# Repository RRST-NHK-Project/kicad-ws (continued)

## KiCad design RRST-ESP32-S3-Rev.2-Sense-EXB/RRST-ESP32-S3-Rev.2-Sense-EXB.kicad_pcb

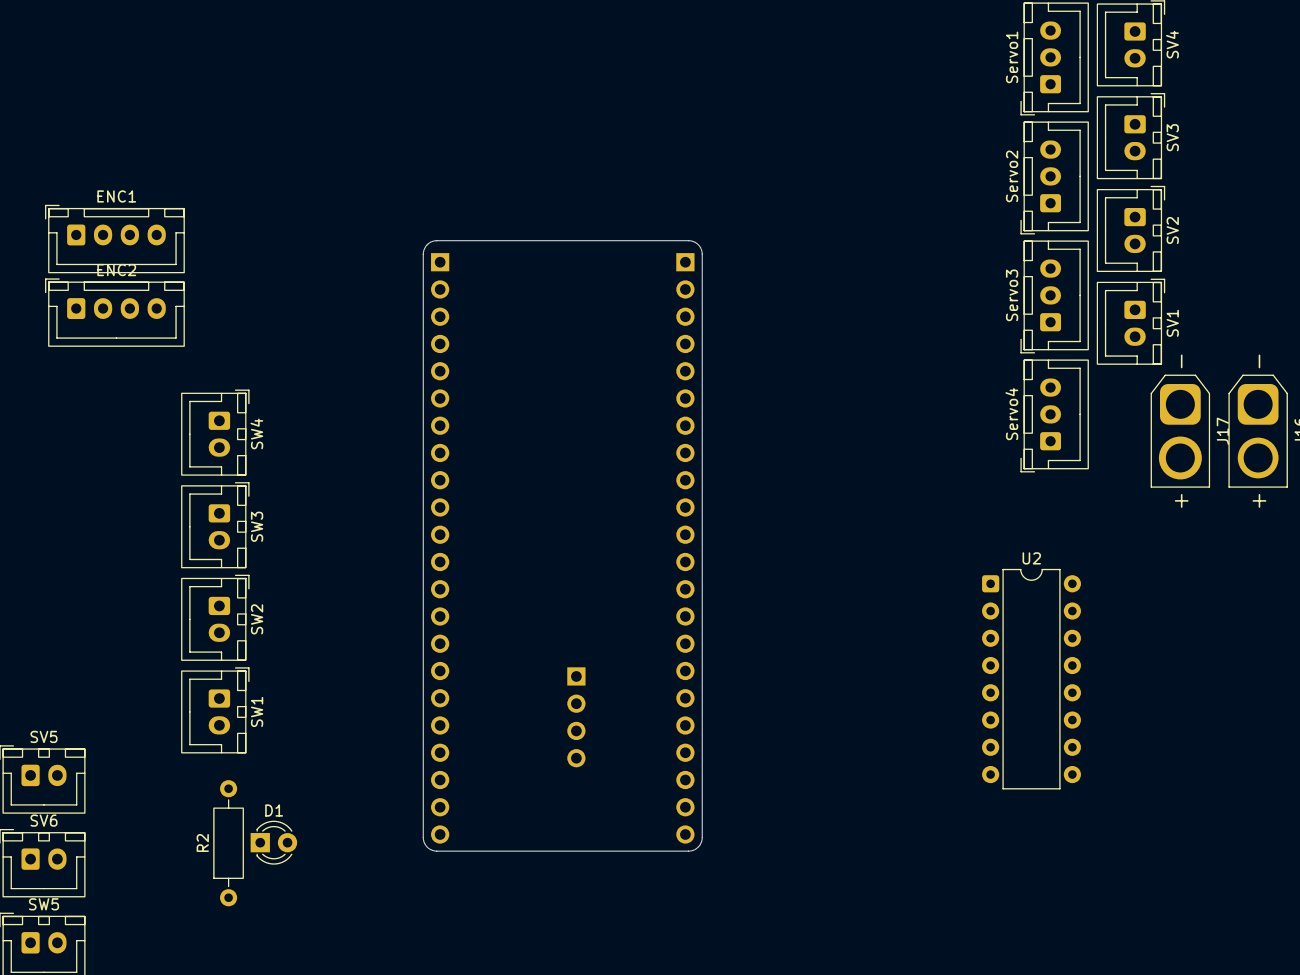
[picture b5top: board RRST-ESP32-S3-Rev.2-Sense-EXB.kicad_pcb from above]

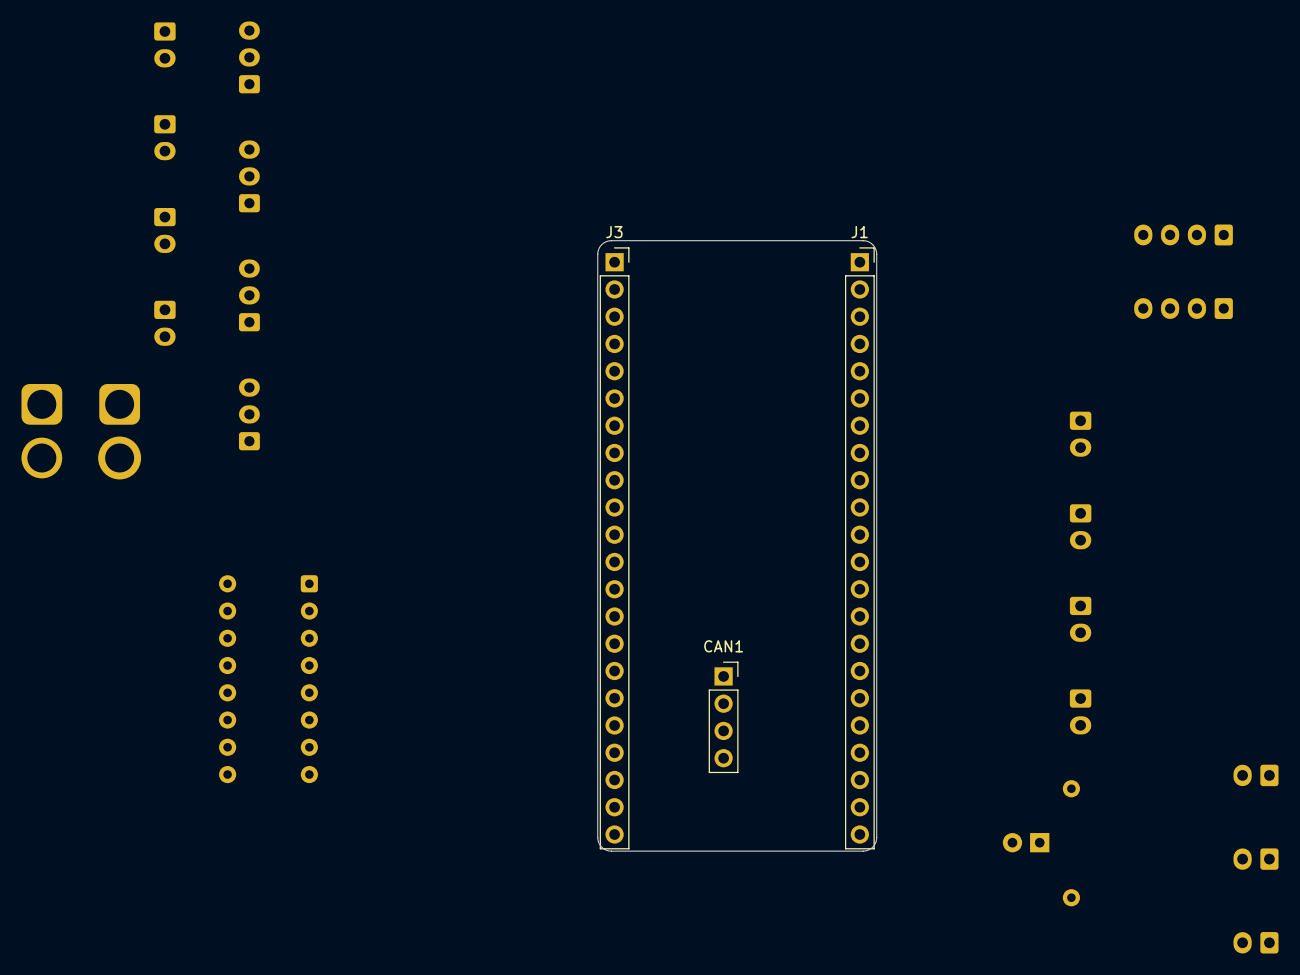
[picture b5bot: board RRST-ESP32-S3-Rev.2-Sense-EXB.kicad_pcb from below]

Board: 2 copper layers, 26.0 x 56.9 mm, 25 parts (3 on the bottom side), 32 nets, no tracks yet.

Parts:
CAN1: CAN; PinSocket_1x04_P2.54mm_Vertical
D1: LED; LED_D3.0mm
ENC1: ENC1; JST_XH_B4B-XH-A_1x04_P2.50mm_Vertical
ENC2: ENC2; JST_XH_B4B-XH-A_1x04_P2.50mm_Vertical
J1, J3: Conn_01x22_Socket; PinSocket_1x22_P2.54mm_Vertical
J16: XT60-M; AMASS_XT30U-M_1x02_P5.0mm_Vertical
J17: XT60-M; AMASS_XT30U-F_1x02_P5.0mm_Vertical
R2: 330; R_Axial_DIN0207_L6.3mm_D2.5mm_P10.16mm_Horizontal
SV1: SV1; JST_XH_B2B-XH-A_1x02_P2.50mm_Vertical
SV2: SV2; JST_XH_B2B-XH-A_1x02_P2.50mm_Vertical
SV3: SV3; JST_XH_B2B-XH-A_1x02_P2.50mm_Vertical
SV4: SV4; JST_XH_B2B-XH-A_1x02_P2.50mm_Vertical
SV5: SV5; JST_XH_B2B-XH-A_1x02_P2.50mm_Vertical
SV6: SV6; JST_XH_B2B-XH-A_1x02_P2.50mm_Vertical
SW1: SW1; JST_XH_B2B-XH-A_1x02_P2.50mm_Vertical
SW2: SW2; JST_XH_B2B-XH-A_1x02_P2.50mm_Vertical
SW3: SW3; JST_XH_B2B-XH-A_1x02_P2.50mm_Vertical
SW4: SW4; JST_XH_B2B-XH-A_1x02_P2.50mm_Vertical
SW5: SW5; JST_XH_B2B-XH-A_1x02_P2.50mm_Vertical
Servo1: Servo1; JST_XH_B3B-XH-A_1x03_P2.50mm_Vertical
Servo2: Servo2; JST_XH_B3B-XH-A_1x03_P2.50mm_Vertical
Servo3: Servo3; JST_XH_B3B-XH-A_1x03_P2.50mm_Vertical
Servo4: Servo4; JST_XH_B3B-XH-A_1x03_P2.50mm_Vertical
U2: DIP-16_W7.62mm

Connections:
3V3: D1.2 (A), J1.1, J1.2
5V0: ENC1.1, ENC2.1, J1.21
+24V: SV1.2, SV2.2, SV3.2, SV4.2, SV5.2, SV6.2, U2.9 (COMMON)
ENC1_A: ENC1.3, J1.18
ENC1_B: ENC1.4, J1.19
ENC2_A: ENC2.3, J1.20
ENC2_B: ENC2.4, J1.8
GND: ENC1.2, ENC2.2, J1.22, J3.1, J3.21, J3.22, SW1.2, SW2.2, SW3.2, SW4.2, SW5.2, Servo1.3, Servo2.3, Servo3.3, Servo4.3, U2.8 (GND)
GPIO0: J3.14, R2.2
GPIO1: J3.4, U2.6 (I6)
GPIO16: J1.9, Servo1.1
GPIO17: J1.10, Servo2.1
GPIO18: J1.11, Servo3.1
GPIO21: J3.18, Servo4.1
GPIO35: J3.13, SW1.1
GPIO36: J3.12, SW2.1
GPIO37: J3.11, SW3.1
GPIO38: J3.10, SW4.1
GPIO39: J3.9, SW5.1
GPIO40: J3.8, U2.1 (I1)
GPIO41: J3.7, U2.2 (I2)
GPIO42: J3.6, U2.3 (I3)
GPIO47: J3.17, U2.4 (I4)
GPIO48: J3.16, U2.5 (I5)
unnamed: D1.1 (K), R2.1
O1: SV1.1, U2.16 (O1)
O2: SV2.1, U2.15 (O2)
O3: SV3.1, U2.14 (O3)
O4: SV4.1, U2.13 (O4)
O5: SV5.1, U2.12 (O5)
O6: SV6.1, U2.11 (O6)
SERVO+: Servo1.2, Servo2.2, Servo3.2, Servo4.2
